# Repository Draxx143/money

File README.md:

# PCB Workbench

A desktop workbench for **analysing printed circuit boards and documenting
diagnostics**, written in C++ with Qt 6 Widgets.

The program reads real board data (KiCad PCB files first), keeps every value
together with its provenance, and helps you work through a fault methodically:
components, nets, test points, measurements, hypotheses and the evidence for and
against each one.

It is an independent implementation. The feature set is intentionally in the same
category as commercial board-analysis tools, but no code, data or asset from such
a tool is used here.

## Status

Milestone 1 (desktop foundation):

* [x] CMake build, C++20, Qt 6 Widgets
* [x] Configurable identity — the product name is configuration, not a constant
* [x] XDG paths, project document with autosave and crash recovery
* [x] Workbench shell: menus, toolbar, dockable panels, board viewer, log viewer
* [x] Settings dialog, English UI, dark industrial palette
* [x] Automated tests (unit, integration, UI) with `ctest`
* [x] `.deb` package

Milestone 2 (real board import):

* [x] KiCad `.kicad_pcb` importer: layers, nets, footprints, pads (with shape,
      rotation and side), tracks, vias and the board outline
* [x] A strict s-expression reader that reports the line and column of a syntax
      error instead of importing a half-read file
* [x] Board outline built from `Edge.Cuts`: lines, rectangles, polygons, arcs and
      circles, joined into closed loops
* [x] Real geometry in the board view: substrate, outline, tracks, vias, pads in
      their own shape, and one clickable group per component
* [x] `File → Import Board File…`, `View → Show Board Back`
* [x] Every skipped element (zones, silkscreen, text, 3D models) is reported as a
      warning on the board and in the log; nothing is invented
* [x] Tests: s-expression reader, importer, and the whole path from a file to the
      explorer and the viewer

Milestone 3 (knowledge base):

* [x] Local SQLite database, schema versioned and migrated, never silently
      recreated when it is damaged
* [x] Component records, filed by part number and manufacturer, with provenance
* [x] Facts with topic, value, conditions and source, full text indexed (FTS5);
      a fact without a source is stored as unverified, nothing is invented
* [x] Component details panel: what the file said, what you completed, the pads
      with their nets, and the knowledge stored about the part
* [x] Importing a board records the part numbers it names, with the board file
      as their source
* [x] Database page in the settings: location, size, counts, integrity check and
      compact
* [x] Tests: 15 database cases (schema, FTS5 search, hostile input, damaged
      file, newer version, reopen) and 3 UI cases for the panel

Milestone 4 (test points and measurements):

* [x] Test points in the project: identifier, component and pad, net, category,
      expected value with a tolerance in absolute terms or in percent, the
      conditions, the instrument, where to put the probes and the source of the
      expectation
* [x] Measurements stored per test point, with instrument, conditions and notes;
      the whole history is kept, the newest one decides the current verdict
* [x] Honest verdicts: `Pass` and `Fail` only where an expected value exists;
      `Unknown` with a reason when there is none or when the units mean
      different things; `Not tested` when nothing was measured yet. Nothing is
      invented, and a missing expectation is never reported as a pass or a fail
* [x] Units are compared by meaning (mV and V are the same quantity, V and A are
      not) and values are scaled into the unit of the expectation before the
      tolerance is applied
* [x] Test points panel: list with the expected value and the newest reading,
      filter, history with the reason for each verdict, and a coverage line
      counting what has really been measured
* [x] Test points and measurements are saved with the project
* [x] Tests: 14 measurement cases (tolerances, edges, percent, units, coverage,
      coverage of what was not measured, round trip through the project) and 3
      UI cases for the panel

Milestone 5 (diagnostic engine):

* [x] Evidence as a first class record: what it is, which way it points, why it
      counts and how trustworthy it is, attached to one hypothesis
* [x] Every weight is explained. A repair counts 3.0, a measurement 2.0, a
      source document 1.0, an observation 0.5, prior knowledge 0.25 -- scaled
      down by how trustworthy it is and halved again when it was only suggested.
      A reading that could not be judged is kept, but weighs nothing
* [x] Honest scores: no evidence means a score of zero and the status
      "possible". One reading confirms nothing however clear it looks; a
      successful repair is the only single piece that confirms on its own
* [x] The status you recorded and the status the evidence suggests are shown
      side by side; the panel never overwrites the user's word
* [x] Candidates built only from data in the project: a reading that failed
      names its net and the parts on it, and every candidate carries the reading
      it came from. When nothing failed, the panel says so instead of inventing
      something
* [x] "Measure next": the test points that would tell us the most, ranked, with
      the reason for each; a reading that proves nothing yet is listed as a gap
      to close, not as a result
* [x] Sessions: title, symptoms, the readings filed under them, and an outcome
* [x] Tests: 19 diagnostic cases and 3 UI cases for the panel

The optional AI assistant follows in a later milestone. It is not advertised as
working today, and there is no menu entry for it yet.

## Building

```bash
cmake -B build -S . -DCMAKE_BUILD_TYPE=Release
cmake --build build
ctest --test-dir build --output-on-failure
cmake --build build --target package    # writes dist/*.deb
```

Requirements: CMake ≥ 3.20, a C++20 compiler and Qt 6 (Core, Gui, Widgets,
Network, Sql, Concurrent, Test, PrintSupport).

On a machine **without** Qt 6 development packages, configure with
`-DUSE_SYSTEM_QT6=OFF` (the default here) after provisioning the toolchain once:

```bash
scripts/toolchain/setup-toolchain.sh
```

That builds `moc` from the Qt sources and points the build at the Qt runtime
libraries that ship with a PySide6 wheel. It exists so that this repository can
be built in a container where the system packages are unavailable; on a normal
development machine use the system Qt and `USE_SYSTEM_QT6=ON`.

## Running the tests

```bash
ctest --test-dir build --output-on-failure
```

The suite redirects the entire application state into a temporary directory
(`PCB_WORKBENCH_HOME`), so it never touches your configuration or projects.

## Packages

```bash
scripts/package-deb.sh          # writes dist/pcb-workbench_<version>_amd64.deb
sudo apt install ./dist/pcb-workbench_0.1.0_amd64.deb
```

Two flavours:

* **Default**: the Qt libraries this build was linked against are installed
  privately under `/usr/lib/pcb-workbench` and are found through the RPATH of the
  binary and the small wrapper script `/usr/bin/pcb-workbench`. The package
  therefore runs on a distribution whose Qt 6 is a different build; it declares
  the host libraries it needs (X11, xcb, GL, ICU-less core, …) as dependencies.
* **`scripts/package-deb.sh --system-qt`**: the package depends on the Qt 6
  packages of the distribution (`libqt6widgets6`, `qt6-qpa-plugins`, …), which is
  what Debian and Ubuntu packaging policy expects. Use this when building *on*
  the target system; the resulting package is smaller and is updated together
  with the rest of the system.

On Ubuntu 24.04 the second variant is the right one, because there Qt 6 comes
from the archive.

## Documentation

* [User manual](docs/UserManual.md)
* [Supported formats](docs/supported_formats.md) — and what is not implemented
* [Architecture](docs/architecture.md)
* [Troubleshooting](docs/troubleshooting.md)
* [Safety](docs/safety.md) — read before probing a live board
* [Data sources and provenance](docs/data_sources.md)

## Licence

MIT — see [LICENSE](LICENSE).

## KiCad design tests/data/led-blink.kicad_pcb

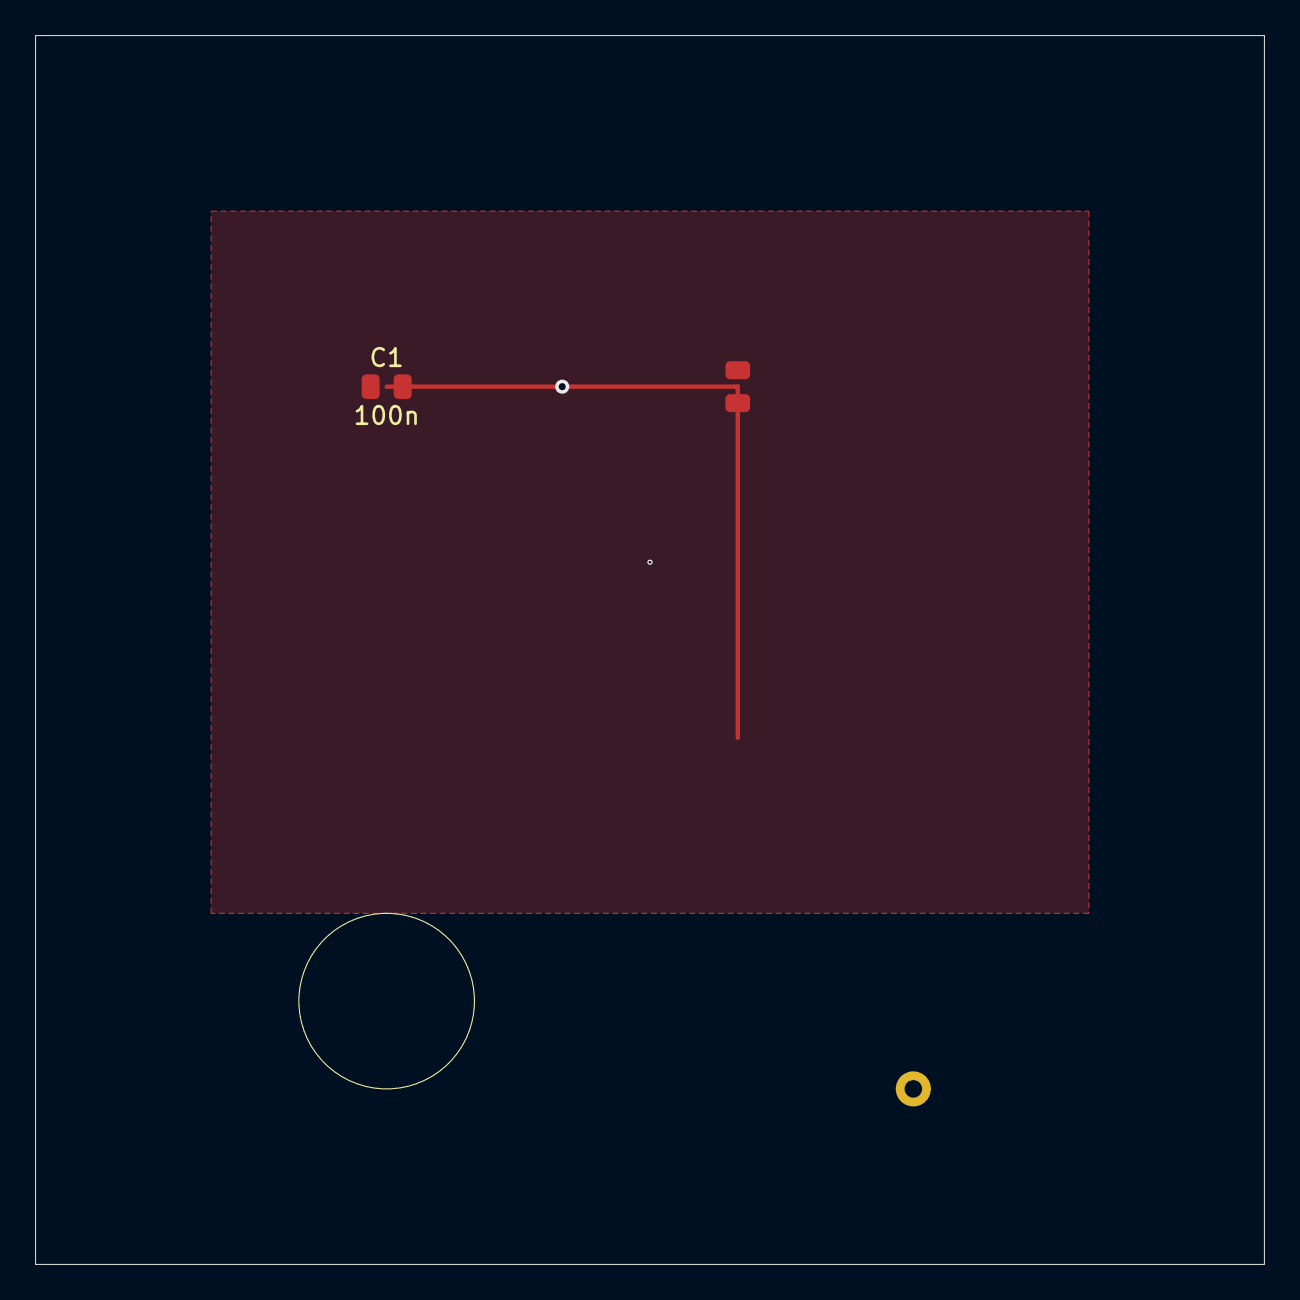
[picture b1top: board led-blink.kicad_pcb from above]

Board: 2 copper layers, 70.0 x 70.0 mm, 4 parts (1 on the bottom side), 3 nets.

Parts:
C1: 100n; C_0805_2012Metric
D1: LED_RED; LED_0805_2012Metric
R1: 330; R_0805_2012Metric
TP1: TestPoint; TestPoint_Pad_2.0mm

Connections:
GND: C1.1, R1.2, TP1.1
LED1: D1.1 (K), R1.1
VCC: C1.2, D1.2 (A)
